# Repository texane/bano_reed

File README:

Door wireless alarm based on a reed switch. It uses the BANO
framework for connectivity. More information on BANO can be
found here:
https://github.com/texane/bano

An introductory blog post can be found here:
http://www.embeddedrelated.com/showarticle/605.php

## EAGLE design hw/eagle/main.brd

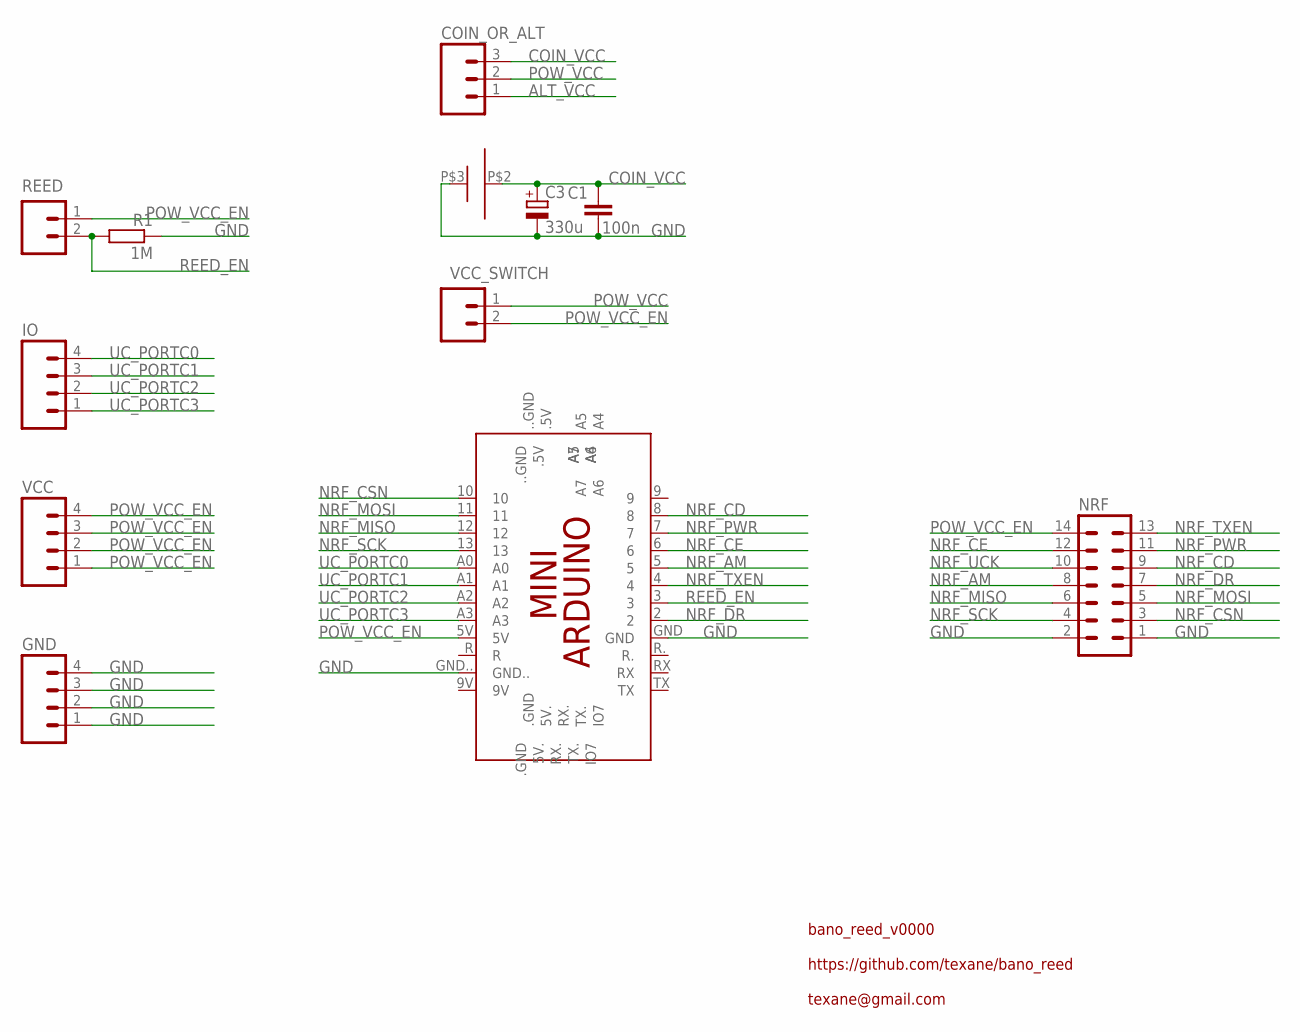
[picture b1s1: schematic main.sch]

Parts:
C1: 100n; C1206K
C3: 330u; PANASONIC_F
COIN_OR_ALT: M03PTH; 1X03
GND: M04PTH; 1X04
IO: M04PTH; 1X04
NRF: MA07-2
PCB1: ARDUINO_MINI
R1: 1M; R1206
REED: M02PTH; 1X02
U$1: KEYSTONE_1025_7
VCC: M04PTH; 1X04
VCC_SWITCH: M02PTH; 1X02

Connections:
ALT_VCC: COIN_OR_ALT.1
COIN_VCC: C1.1, C3.+, COIN_OR_ALT.3, U$1.P$2 (COIN_PLUS)
GND: C1.2, C3.-, GND.1, GND.2, GND.3, GND.4, NRF.1, NRF.2, PCB1.GND, PCB1.GND.., R1.1, U$1.P$3 (COIN_MINUS)
NRF_AM: NRF.8, PCB1.5
NRF_CD: NRF.9, PCB1.8
NRF_CE: NRF.12, PCB1.6
NRF_CSN: NRF.3, PCB1.10
NRF_DR: NRF.7, PCB1.2
NRF_MISO: NRF.6, PCB1.12
NRF_MOSI: NRF.5, PCB1.11
NRF_PWR: NRF.11, PCB1.7
NRF_SCK: NRF.4, PCB1.13
NRF_TXEN: NRF.13, PCB1.4
NRF_UCK: NRF.10
POW_VCC: COIN_OR_ALT.2, VCC_SWITCH.1
POW_VCC_EN: NRF.14, PCB1.5V, REED.1, VCC.1, VCC.2, VCC.3, VCC.4, VCC_SWITCH.2
REED_EN: PCB1.3, R1.2, REED.2
UC_PORTC0: IO.4, PCB1.A0
UC_PORTC1: IO.3, PCB1.A1
UC_PORTC2: IO.2, PCB1.A2
UC_PORTC3: IO.1, PCB1.A3

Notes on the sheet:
bano_reed_v0000
https://github.com/texane/bano_reed
texane@gmail.com

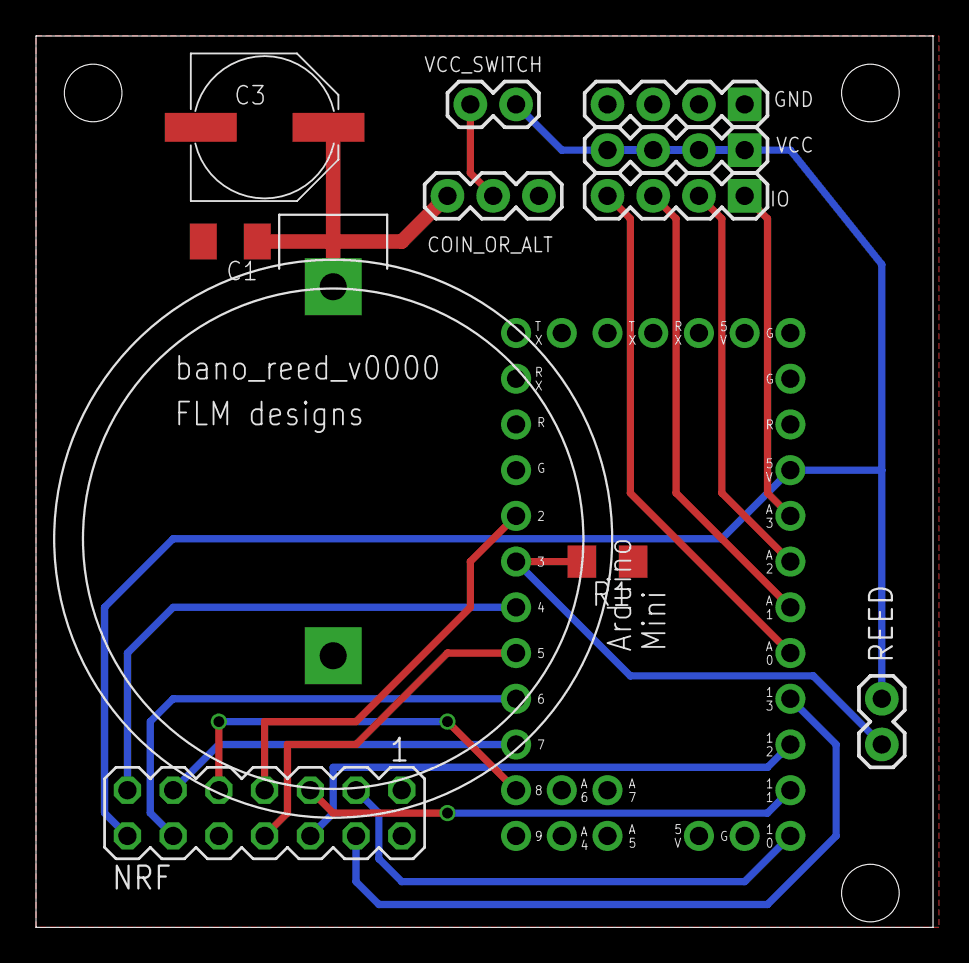
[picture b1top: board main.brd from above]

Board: 2 copper layers, 49.8 x 49.5 mm, 12 parts (0 on the bottom side), 19 nets.

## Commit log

2014-02-17 [ add ] doc
2014-02-17 [ add ] src
2014-02-17 [ add ] src/bano
2014-02-17 [ update ] bano, disable all but USART
2014-02-17 [ update ] BANO_CONFIG_NRF905
2014-02-18 [ update ] remove BANO_CONFIG_NRF905
2014-02-19 [ update ] send fake keyval
2014-02-22 [ update ] CONFIG_LED
2014-02-23 [ add ] main_1.0.hex
2014-03-08 [ add ] doc/pic
2014-03-09 [ update ] makefile to use new bano repo
2014-03-09 [ add ] doc/notes, building
2014-03-09 [ update ] doc/notes
2014-03-09 [ rename ] main_1.0.hex to avoid cleaned at make
2014-03-09 [ rename ] main_1.0.hex.bak to avoid cleaned at make
2014-03-09 [ update ] doc/notes, capacitors
2014-03-26 [ mv, add ] rename bano into node, add base source code
2014-04-01 [ update ] generate node addr and seed in makefile
2014-04-05 [ rm, add ] rm minipro_3v3.mk, use Makefile
2014-04-05 [ rm ] rm upload_3v3.mk, included in Makefile
2014-04-05 [ update ] bano_node implementation included by header file
2014-04-05 [ update ] Makefile
2014-04-06 [ update ] nodl_id statically defined
2014-04-06 [ update ] BANO_BOARD
2014-04-07 [ update ] use BANO_FLAG_ERR
2014-04-11 [ update ] BANO_MSG_xxx
2014-05-05 [ update ] fix node address. send only on 0 to 1 transition.
2014-05-13 [ update ] get_vcc
2014-05-13 [ fix ] missing include
2014-05-13 [ update ] get_vcc sum more values
2014-05-16 [ add ] hw
2014-05-16 [ add ] main.bom
2014-05-16 [ update ] main.bom, todos
2014-05-16 [ update ] route, wip
2014-05-16 [ update ] schematics progress
2014-05-16 [ add ] hw todos
2014-05-16 [ add ] hw board, to be routed
2014-05-16 [ add ] hw, wip
2014-05-16 [ update ] route, done. footprints to be checked
2014-05-16 [ add ] keystone_1025_7.lbr
2014-05-16 [ update ] route, done. dimension checks needed
2014-05-17 [ add ] board routing, done
2014-05-17 [ update ] bom
2014-05-17 [ update ] gerber
2014-06-03 [ add ] doc/related
2014-06-03 [ add ] pics
2014-06-04 [ fix ] typo
2014-06-09 [ add ] README
2014-06-10 [ rm ] doc/related
2014-06-10 [ rm ] base. use to bano repo
2014-06-10 [ rm ] hex file
2014-06-11 [ update ] README

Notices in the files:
parts and their libraries:
SparkFun: Licensing: CC v3.0 Share-Alike You are welcome to use this library for commercial purposes.
